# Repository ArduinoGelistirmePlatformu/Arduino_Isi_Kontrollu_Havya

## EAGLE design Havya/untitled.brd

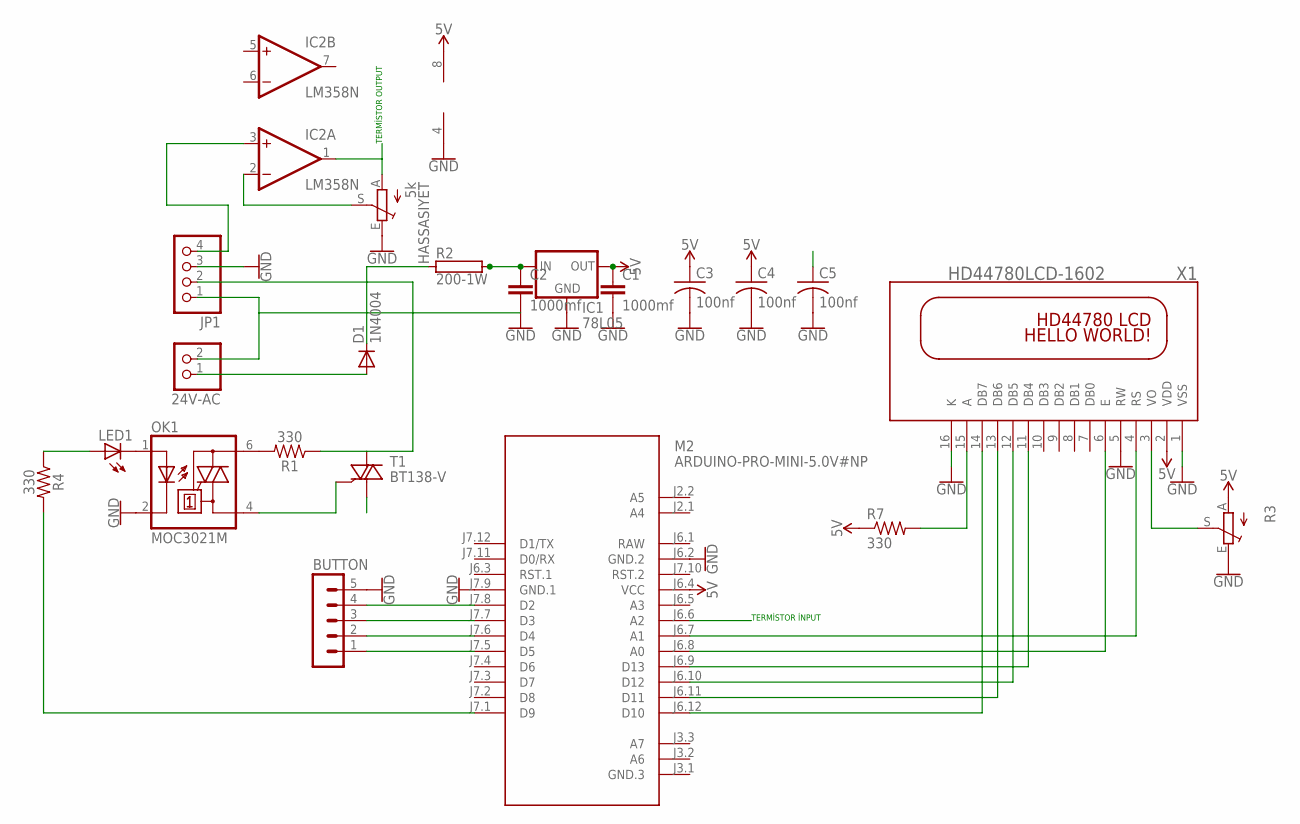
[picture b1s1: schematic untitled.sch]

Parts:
24V-AC: PINHD-1X2; 1X02
BUTTON: MA05-1
C1, C2: 1000mf; C5B3.5
C3, C4, C5: 100nf; C1206
D1: 1N4004; DO41-10
HASSASIYET: 5k; S64W
IC1: 78L05; 78MXXS
IC2: LM358N; DIL08
JP1: PINHD-1X4; 1X04
LED1: LED3MM
M2: ARDUINO-PRO-MINI-5.0V#NP; ARDUINO-PRO-MINI#NP
OK1: MOC3021M; DIL06
R1, R4: 330; AXIAL-0.3
R2: 200-1W; KH206-8R
R3: TRIM_EU-CA6V; CA6V
R7: 330; 0207/10
T1: BT138-V; TO220BV
X1: HD44780LCD-1602; LCD1602

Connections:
5V: C1.1, C3.1, C4.1, IC1.OUT, IC2.8 (V+), M2.J6.4 (VCC), R3.A, R7.1, X1.2 (VDD)
24V: C2.1, C5.1, IC1.IN, R2.2
A2: HASSASIYET.A, IC2.1 (OUT), M2.J6.6 (A2)
GND: 24V-AC.2, BUTTON.5, C1.2, C2.2, C3.2, C4.2, C5.2, HASSASIYET.E, IC1.GND, IC2.4 (V-), JP1.1, JP1.3, M2.J6.2 (GND.2), M2.J7.9 (GND.1), OK1.2 (C), R3.E, X1.1 (VSS), X1.5 (RW), X1.16 (K)
unnamed: M2.J6.12 (D10), X1.14 (DB7)
unnamed: BUTTON.4, M2.J7.8 (D2)
unnamed: LED1.K (C), OK1.1 (A)
unnamed: OK1.6 (A2), R1.P$2 (2)
unnamed: OK1.4 (A1), T1.G
unnamed: JP1.2, R1.P$1 (1), T1.T2 (A2)
unnamed: M2.J6.11 (D11), X1.13 (DB6)
unnamed: M2.J6.8 (A0), X1.6 (E)
unnamed: D1.C, R2.1
unnamed: R3.S, X1.3 (VO)
unnamed: M2.J6.10 (D12), X1.12 (DB5)
unnamed: M2.J6.9 (D13), X1.11 (DB4)
unnamed: M2.J6.7 (A1), X1.4 (RS)
unnamed: LED1.A, R4.P$1 (1)
unnamed: M2.J7.1 (D9), R4.P$2 (2)
unnamed: R7.2, X1.15 (A)
unnamed: IC2.3 (+IN), JP1.4
unnamed: HASSASIYET.S, IC2.2 (-IN)
unnamed: BUTTON.3, M2.J7.7 (D3)
unnamed: BUTTON.2, M2.J7.6 (D4)
unnamed: BUTTON.1, M2.J7.5 (D5)
unnamed: 24V-AC.1, D1.A, T1.T1 (A1)
RAW: M2.J6.1 (RAW)

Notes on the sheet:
TERMİSTOR İNPUT
TERMİSTOR OUTPUT

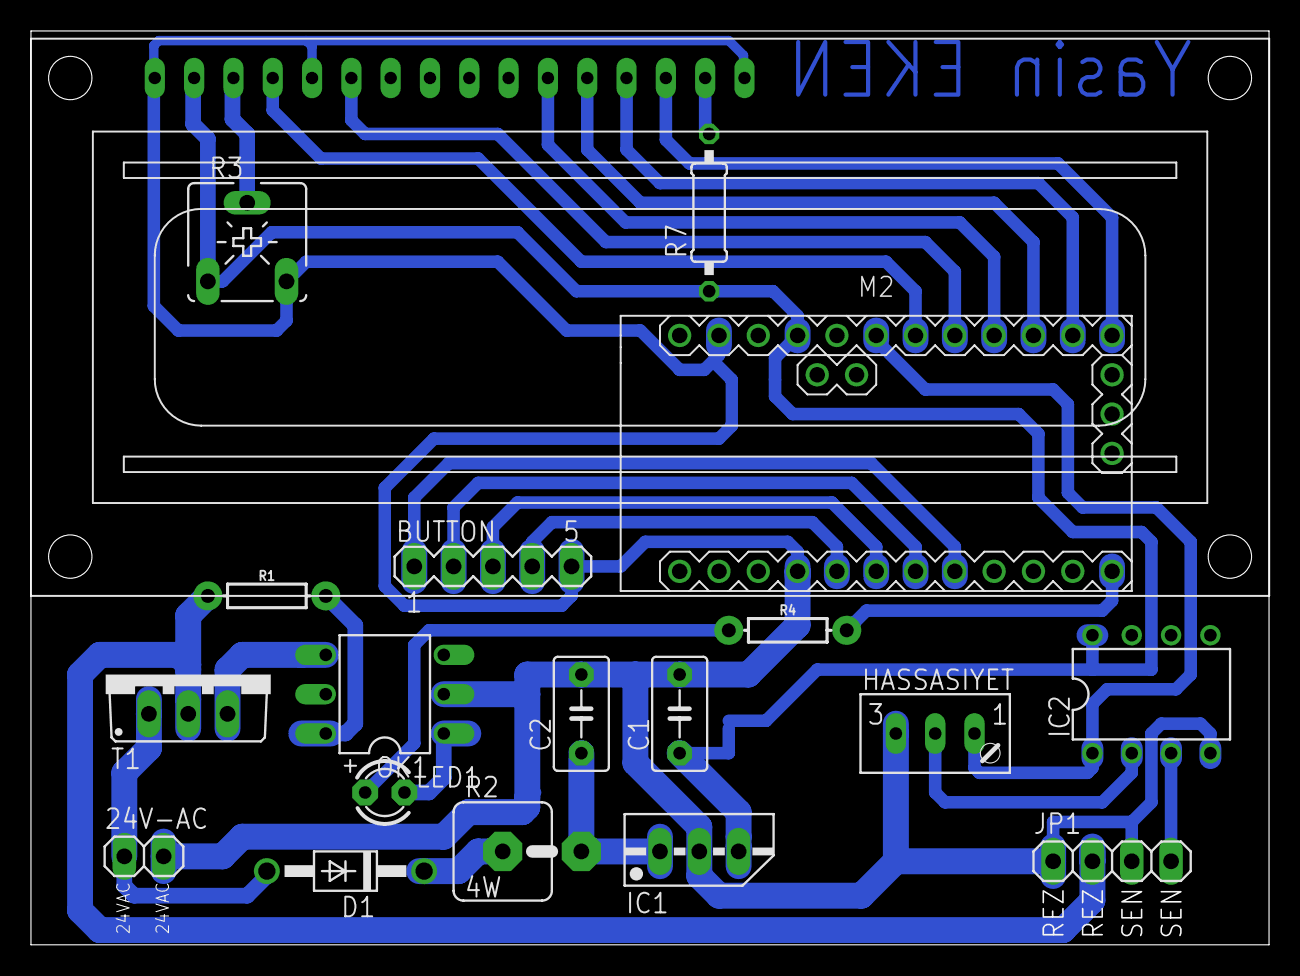
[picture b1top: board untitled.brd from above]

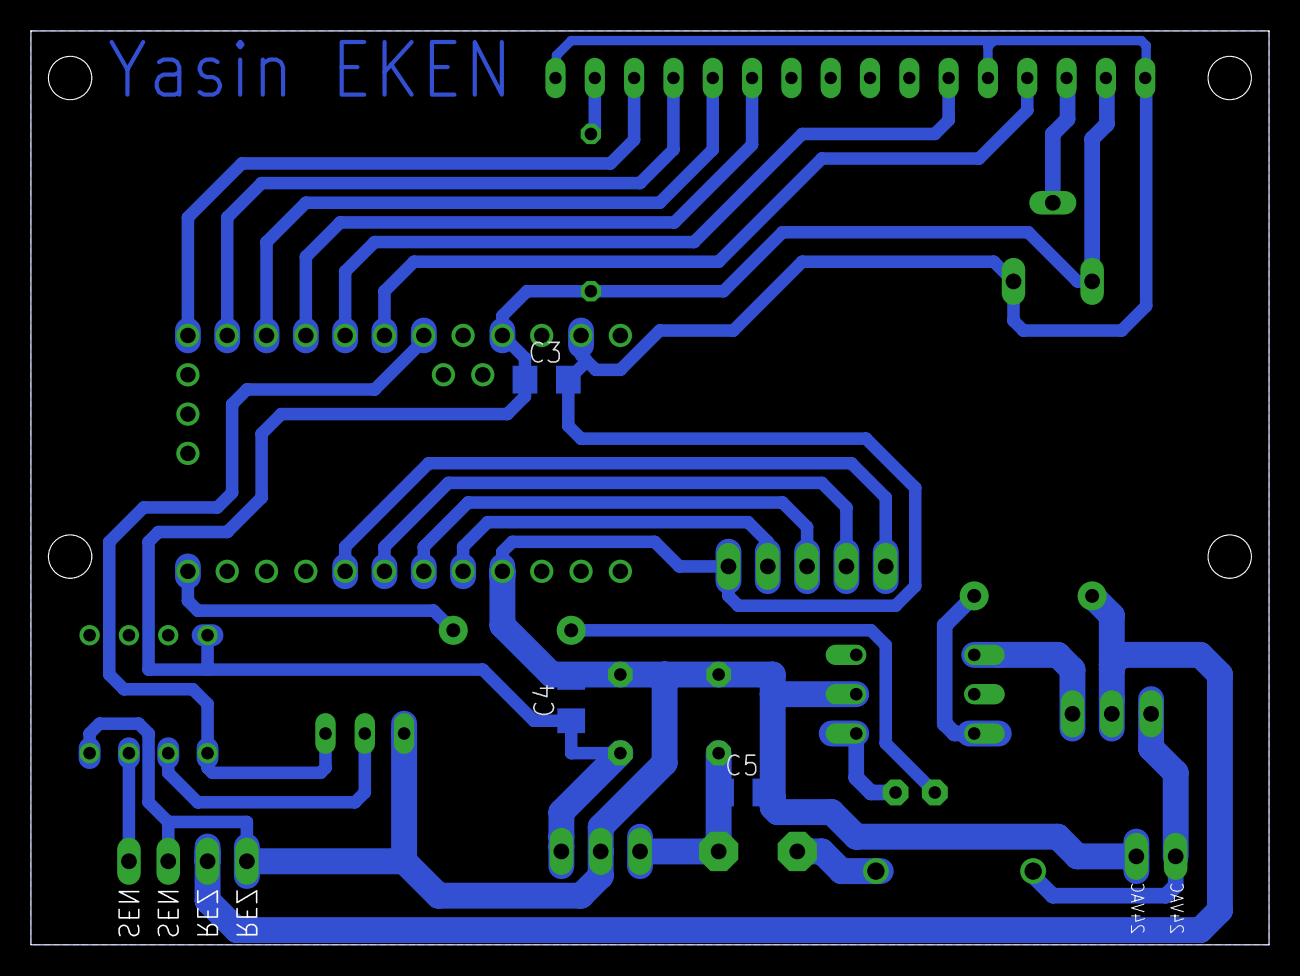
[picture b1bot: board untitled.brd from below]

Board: 2 copper layers, 80.0 x 59.0 mm, 22 parts (3 on the bottom side), 26 nets.

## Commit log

2017-12-02 :space_invader: Added .gitattributes & .gitignore files
2017-12-02 Arduino Isı Kontrollü Havya
    Arduino Isı Kontrollü Havya
2017-12-02 Arduino ısı kontrollü havya
    Arduino ısı kontrollü havya
2017-12-02 Arduino ısı kontrollü havya v2
    Arduino ısı kontrollü havya v2

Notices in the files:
parts and their libraries:
diy-modules: Released under the Creative Commons Attribution 4.0 International License: http://creativecommons.org/licenses/by/4.0
SparkFun-Resistors: Licensing: Creative Commons ShareAlike 4.0 International - https://creativecommons.org/licenses/by-sa/4.0
